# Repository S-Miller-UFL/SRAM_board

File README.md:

This is a breakout board for the stm32f072 main mcu board.

it contains an is61lv256al-10tli sram chip, and an AT25SF081 flash chip.

It also contains a transistory that acts as a chip select by pulling one of the memory chips' CS lines high while its writing to the other one.

This board is just needs to be placed on top of the main stm32f072 board, and its ready to go.

It was built using KICAD. Its traced, routed, and ready to be manufactured.

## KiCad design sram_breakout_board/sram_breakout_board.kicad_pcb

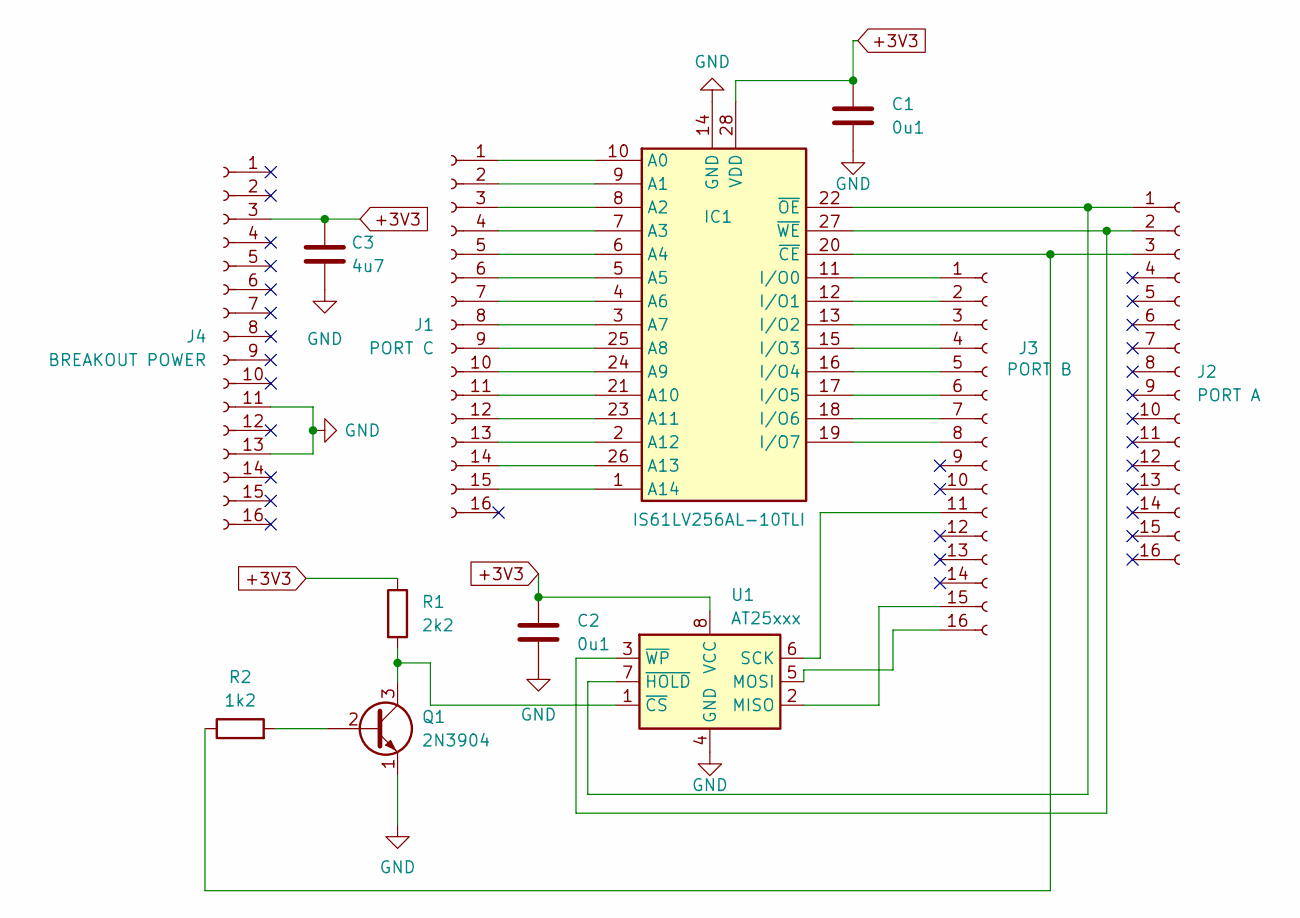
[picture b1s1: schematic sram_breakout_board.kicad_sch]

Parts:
C1, C2: 0u1; C_0402_1005Metric
C3: 4u7; C_0402_1005Metric
IC1: IS61LV256AL-10TLI; TSOP-I-28_11.8x8mm_P0.55mm; Mouser Part Number 870-IS61LV256AL10TLI
J1: PORT C; PinSocket_1x16_P2.00mm_Vertical
J2: PORT A; PinSocket_1x16_P2.00mm_Vertical
J3: PORT B; PinSocket_1x16_P2.00mm_Vertical
J4: BREAKOUT POWER; PinSocket_1x16_P2.00mm_Vertical
Q1: 2N3904; TO-92_Inline
R1: 2k2; R_0402_1005Metric
R2: 1k2; R_0402_1005Metric
U1: AT25xxx; SOIC-8-1EP_3.9x4.9mm_P1.27mm_EP2.29x3mm

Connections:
+3V3: C1.1, C2.1, C3.1, IC1.28 (VDD), J4.3, R1.1, U1.8 (VCC)
GND: C1.2, C2.2, C3.2, IC1.14 (GND), J4.11, J4.13, Q1.1 (E), U1.4 (GND)
unnamed: IC1.10 (A0), J1.1
unnamed: IC1.9 (A1), J1.2
unnamed: IC1.8 (A2), J1.3
unnamed: IC1.7 (A3), J1.4
unnamed: IC1.6 (A4), J1.5
unnamed: IC1.5 (A5), J1.6
unnamed: IC1.4 (A6), J1.7
unnamed: IC1.3 (A7), J1.8
unnamed: IC1.25 (A8), J1.9
unnamed: IC1.24 (A9), J1.10
unnamed: IC1.21 (A10), J1.11
unnamed: IC1.23 (A11), J1.12
unnamed: IC1.2 (A12), J1.13
unnamed: IC1.26 (A13), J1.14
unnamed: IC1.1 (A14), J1.15
unnamed: IC1.11 (I/O0), J3.1
unnamed: IC1.12 (I/O1), J3.2
unnamed: IC1.13 (I/O2), J3.3
unnamed: IC1.15 (I/O3), J3.4
unnamed: IC1.16 (I/O4), J3.5
unnamed: IC1.17 (I/O5), J3.6
unnamed: IC1.18 (I/O6), J3.7
unnamed: IC1.19 (I/O7), J3.8
unnamed: IC1.20 (~CE), J2.3, R2.1
unnamed: IC1.22 (~OE), J2.1, U1.7 (~HOLD)
unnamed: IC1.27 (~WE), J2.2, U1.3 (~WP)
unnamed: J3.11, U1.6 (SCK)
unnamed: J3.15, U1.2 (MISO)
unnamed: J3.16, U1.5 (MOSI)
unnamed: Q1.2 (B), R2.2
unnamed: Q1.3 (C), R1.2, U1.1 (~CS)

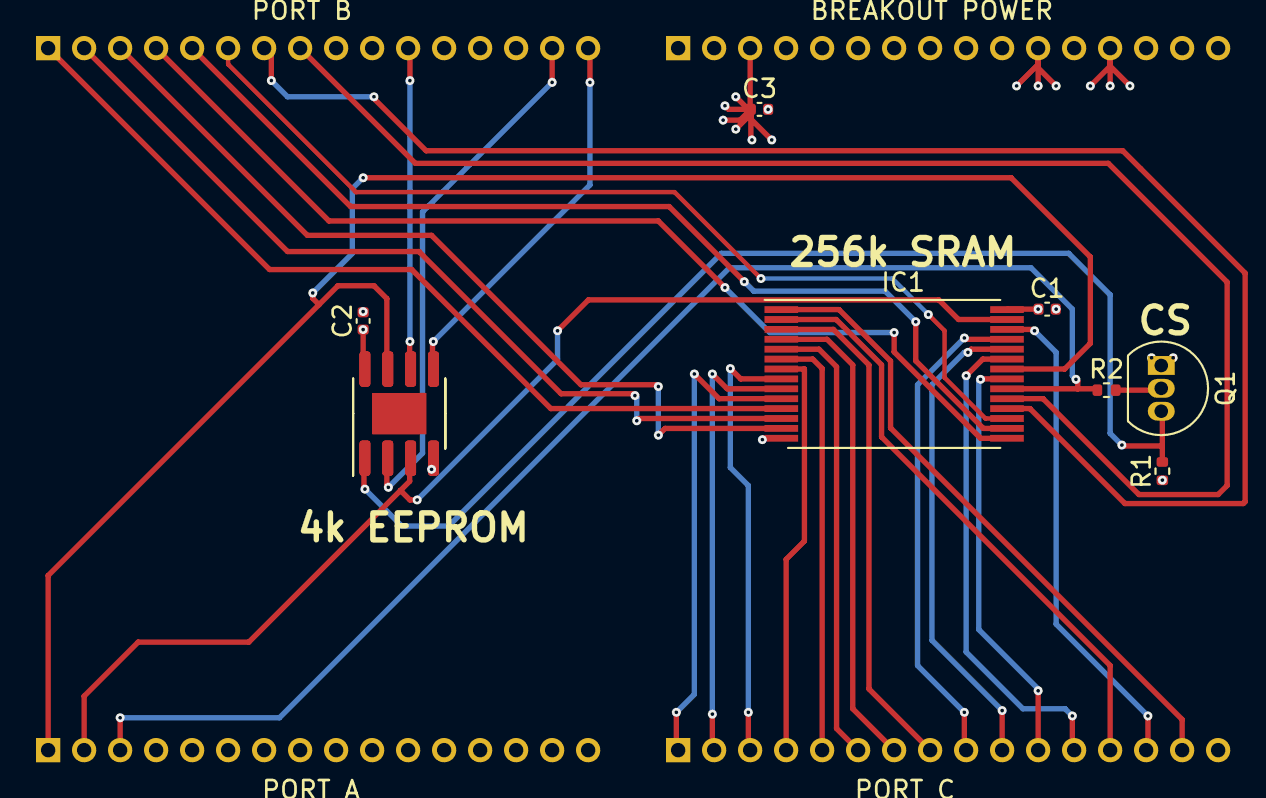
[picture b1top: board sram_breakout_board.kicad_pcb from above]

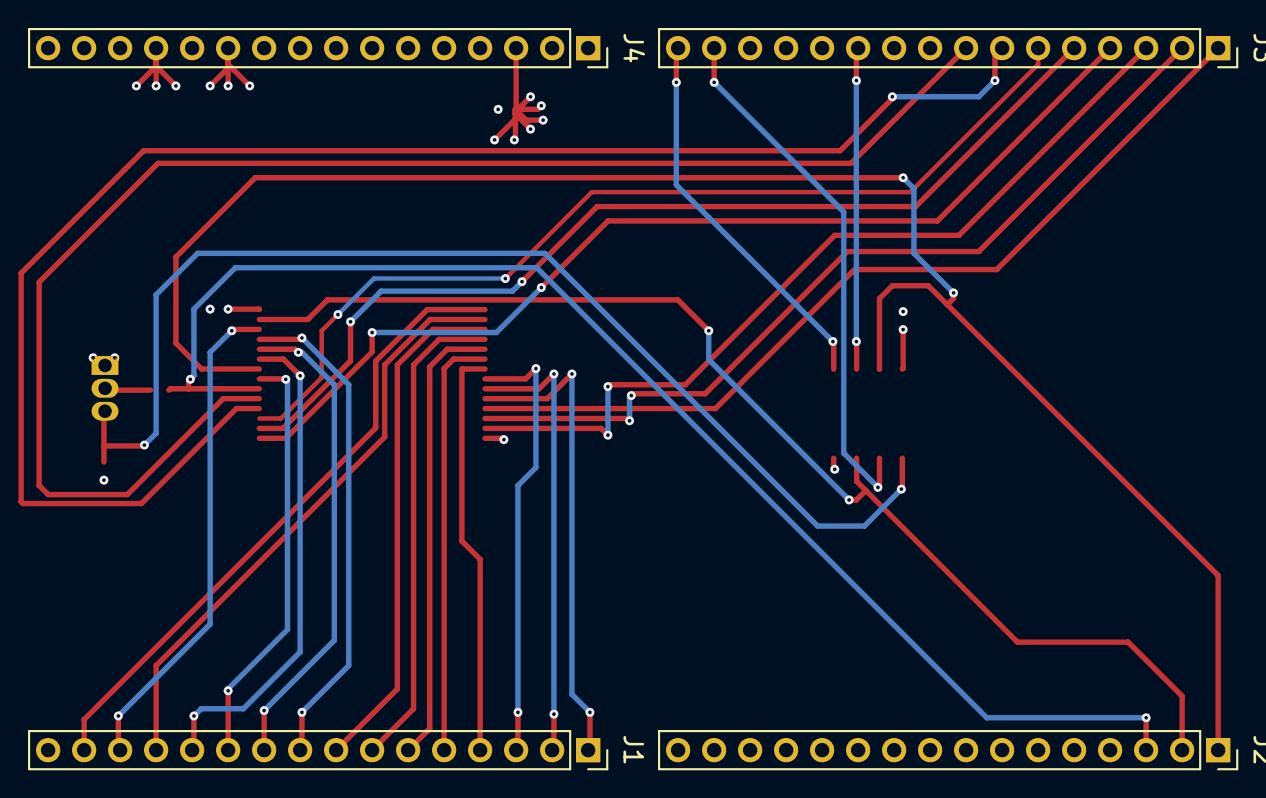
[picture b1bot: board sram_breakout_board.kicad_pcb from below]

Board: 4 copper layers, 12 parts (4 on the bottom side), 33 nets.

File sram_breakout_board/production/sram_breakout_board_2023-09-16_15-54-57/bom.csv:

Designator,Footprint,Quantity,Value,LCSC Part #
"C1, C2",0402,2,0u1,
C3,0402,1,4u7,
IC1,TSOP-I-28_11.8x8mm_P0.55mm,1,IS61LV256AL-10TLI,
J1,PinSocket_1x16_P2.00mm_Vertical,1,PORT C,
J2,PinSocket_1x16_P2.00mm_Vertical,1,PORT A,
J3,PinSocket_1x16_P2.00mm_Vertical,1,PORT B,
J4,PinSocket_1x16_P2.00mm_Vertical,1,BREAKOUT POWER,
Q1,TO-92_Inline,1,2N3904,
R1,0402,1,2k2,
R2,0402,1,1k2,
U1,SOIC-8-1EP_3.9x4.9mm_P1.27mm_EP2.29x3mm,1,AT25xxx,

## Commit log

2024-12-27 Created README.md
